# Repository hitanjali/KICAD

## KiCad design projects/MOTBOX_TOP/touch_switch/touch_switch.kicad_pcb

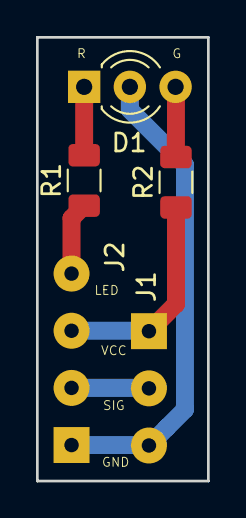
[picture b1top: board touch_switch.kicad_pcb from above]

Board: 2 copper layers, 9.5 x 24.6 mm, 5 parts (0 on the bottom side), 6 nets.

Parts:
D1: LED_Dual_ACA; LED_D3.0mm-3
J1: Conn_01x03; SolderWirePad_1x03_P3.175mm_Drill0.8mm
J2: Conn_01x04; SolderWirePad_1x04_P3.175mm_Drill0.8mm
R1, R2: 150R; R_1206_3216Metric

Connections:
unnamed: D1.1, R1.2
unnamed: D1.2, J1.3, J2.1
unnamed: D1.3, R2.2
unnamed: J1.1, J2.3, R2.1
unnamed: J1.2, J2.2
unnamed: J2.4, R1.1

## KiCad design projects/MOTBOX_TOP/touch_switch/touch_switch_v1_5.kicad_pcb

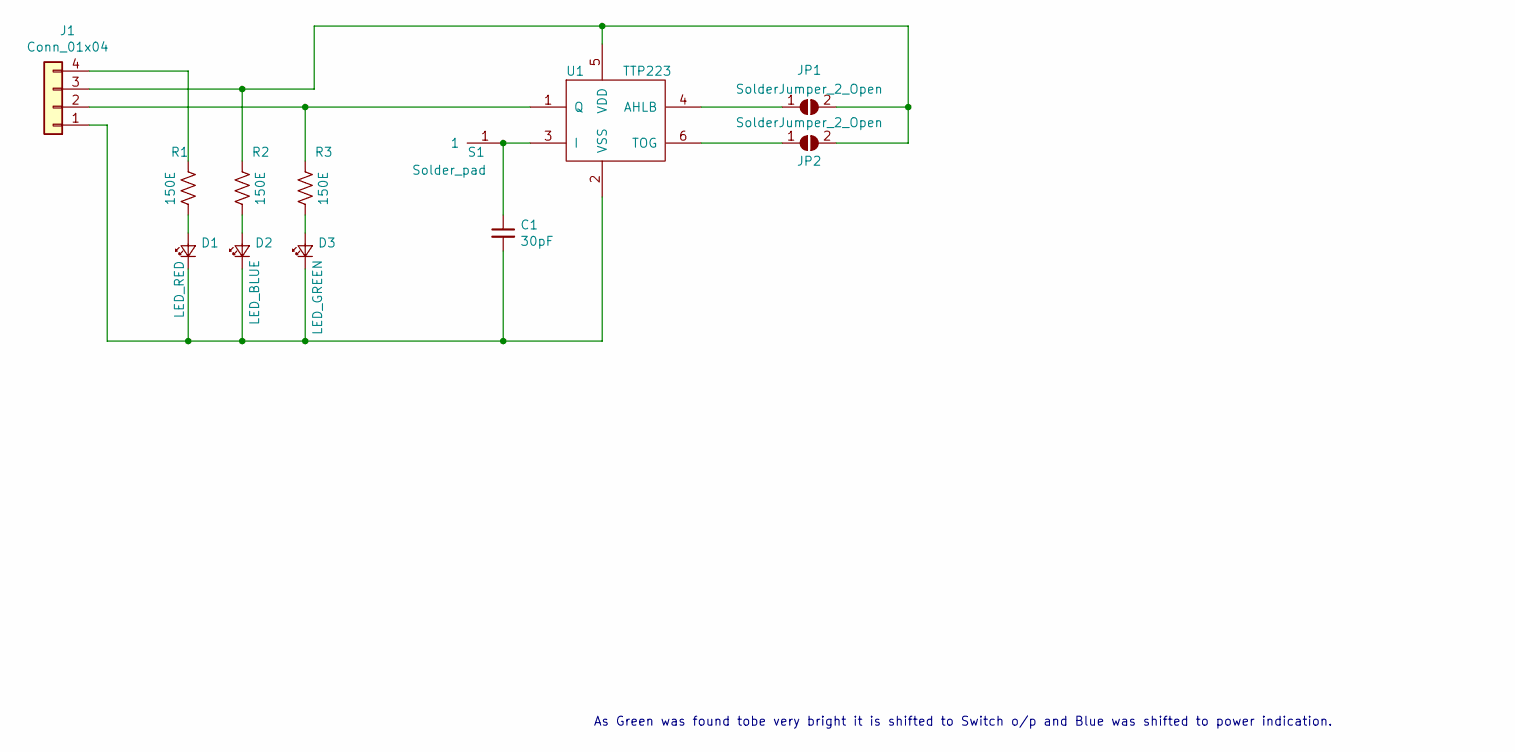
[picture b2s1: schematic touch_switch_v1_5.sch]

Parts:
C1: 30pF; C_0603_1608Metric
D1: LED_RED; LED_0603_1608Metric
D2: LED_BLUE; LED_0603_1608Metric
D3: LED_GREEN; LED_0603_1608Metric
J1: Conn_01x04; SolderWirePad_1x04_P3.175mm_Drill0.8mm
JP1, JP2: SolderJumper_2_Open; SolderJumper-2_P1.3mm_Open_RoundedPad1.0x1.5mm
R1, R2, R3: 150E; R_0603_1608Metric
S1: Solder_pad; Touch_pad_10x10mm
U1: TTP223; SOT-23-6

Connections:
unnamed: C1.1, S1.1, U1.3 (I)
unnamed: C1.2, D1.1 (K), D2.1 (K), D3.1 (K), J1.1, U1.2 (VSS)
unnamed: D1.2 (A), R1.2
unnamed: D2.2 (A), R2.2
unnamed: D3.2 (A), R3.2
unnamed: J1.2, R3.1, U1.1 (Q)
unnamed: J1.3, JP1.2 (B), JP2.2 (B), R2.1, U1.5 (VDD)
unnamed: J1.4, R1.1
unnamed: JP1.1 (A), U1.4 (AHLB)
unnamed: JP2.1 (A), U1.6 (TOG)

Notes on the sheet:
As Green was found tobe very bright it is shifted to Switch o/p and Blue was shifted to power indication.

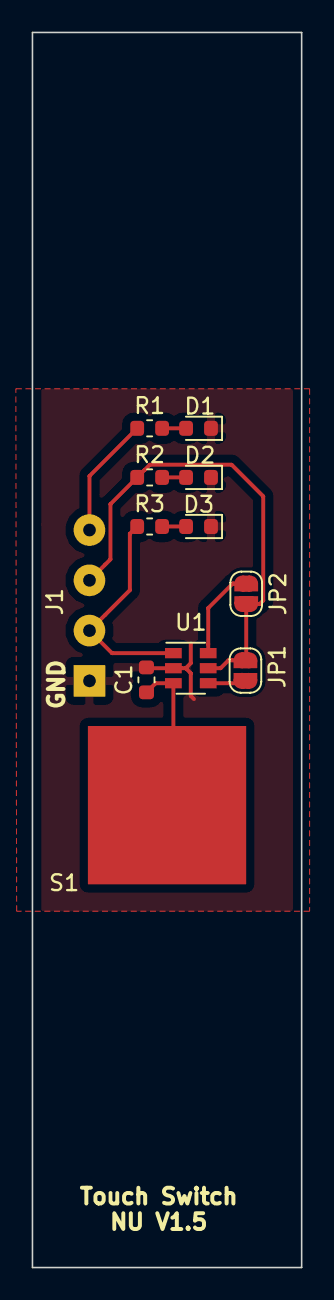
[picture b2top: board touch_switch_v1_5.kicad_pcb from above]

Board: 2 copper layers, 17.0 x 78.0 mm, 12 parts (0 on the bottom side), 10 nets.

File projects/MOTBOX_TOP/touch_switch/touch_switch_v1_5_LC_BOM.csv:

S.No,Manufacturing Part No,Designator,Quantity,Description(VALUE),Package(CASE),Top/Bottom,Points (No. of Pins),Comments,,
1,  , "C1, " , "1" , "30pF" , "Capacitor_SMD:C_0603_1608Metric" , TOP , 2, "Unpolarized capacitor, small symbol", , 
2,  , "D1, " , "1" , "LED_RED" , "LED_SMD:LED_0603_1608Metric" , TOP , 2, "Light emitting diode, small symbol", , 
3,  , "D2, " , "1" , "LED_GREEN" , "LED_SMD:LED_0603_1608Metric" , TOP , 2, "Light emitting diode, small symbol", , 
4,  , "D3, " , "1" , "LED_BLUE" , "LED_SMD:LED_0603_1608Metric" , TOP , 2, "Light emitting diode, small symbol", , 
5,  , "J1, " , "1" , "Conn_01x04" , "Connector_Wire:SolderWirePad_1x04_P3.175mm_Drill0.8mm" , TOP , 4, "Generic connector, single row, 01x04, script generated (kicad-library-utils/schlib/autogen/connector/)", , 
6,  , "JP1, JP2, " , "2" , "SolderJumper_2_Open" , "Jumper:SolderJumper-2_P1.3mm_Open_RoundedPad1.0x1.5mm" , TOP , 2, "Solder Jumper, 2-pole, open", , 
7,  , "R1, R2, R3, " , "3" , "150E" , "Resistor_SMD:R_0603_1608Metric" , TOP , 2, "Resistor, US symbol", , 
8,  , "S1, " , "1" , "Solder_pad" , "mylib:Touch_pad_10x10mm" , TOP , 1, "", , 
9,  , "U1, " , "1" , "TTP223" , "Package_TO_SOT_SMD:SOT-23-6" , TOP , 6, "", ,

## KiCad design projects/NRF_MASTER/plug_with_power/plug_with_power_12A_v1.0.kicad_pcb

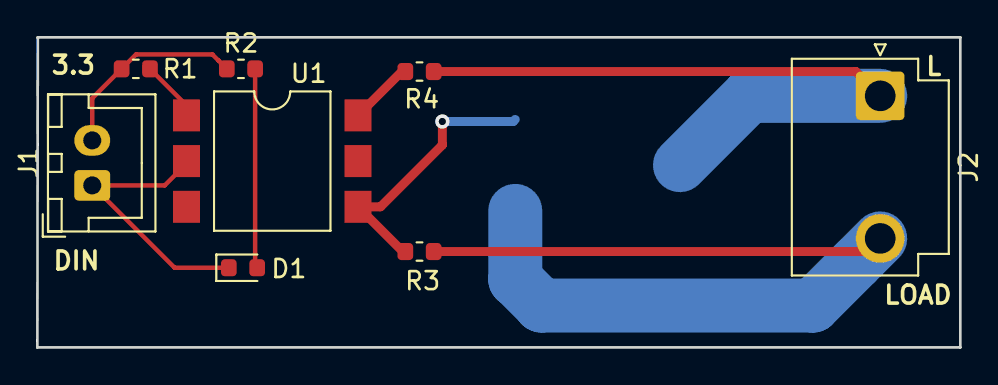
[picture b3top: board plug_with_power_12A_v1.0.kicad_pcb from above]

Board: 2 copper layers, 51.3 x 17.2 mm, 9 parts (1 on the bottom side), 8 nets.

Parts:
D1: YELLOW; LED_0603_1608Metric
D2: T12XX-600G; TO-263-2
J1: Conn_01x02; JST_XH_B2B-XH-A_1x02_P2.50mm_Vertical
J2: Conn_01x02; JST_VH_B2P3-VH_1x02_P7.92mm_Vertical
R1, R2: 220; R_0603_1608Metric
R3: 330; R_0603_1608Metric
R4: 360; R_0603_1608Metric
U1: MOC3083S; SMDIP-6_W9.53mm_Clearance8mm

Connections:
/ACHC1: D2.1, J2.2, R3.1
/ACHC2: D2.2, J2.1, R4.1
unnamed: D1.1, J1.1, U1.2
unnamed: D1.2, R2.2
unnamed: D2.3, R3.2, U1.4
unnamed: J1.2, R1.2, R2.1
unnamed: R1.1, U1.1
unnamed: R4.2, U1.6

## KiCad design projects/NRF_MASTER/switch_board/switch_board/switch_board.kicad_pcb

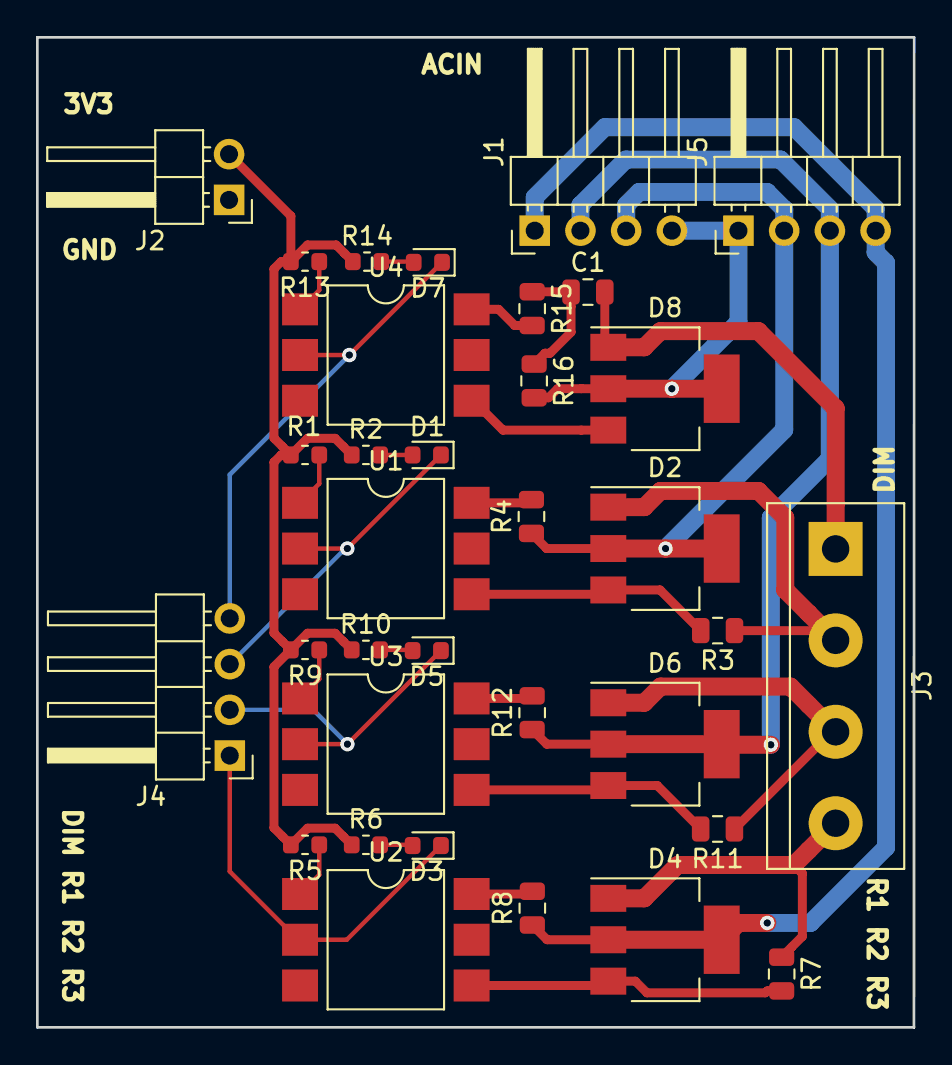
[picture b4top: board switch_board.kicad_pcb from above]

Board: 2 copper layers, 48.7 x 55.0 mm, 34 parts (0 on the bottom side), 30 nets.

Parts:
C1: C_Small; C_0805_2012Metric
D1, D3, D5, D7: YELLOW; LED_0603_1608Metric
D2, D4, D6, D8: Z0103MN; SOT-223
J1, J4, J5: Conn_01x04; PinHeader_1x04_P2.54mm_Horizontal
J2: Conn_01x02; PinHeader_1x02_P2.54mm_Horizontal
J3: Conn_01x04; TerminalBlock_bornier-4_P5.08mm
R1, R2, R5, R6, R9, R10, R13, R14: 220; R_0603_1608Metric
R3, R7, R11: 330; R_0805_2012Metric
R4, R8, R12, R15: 360; R_0805_2012Metric
R16: 470; R_0805_2012Metric
U1, U2, U3: MOC3083S; SMDIP-6_W9.53mm
U4: MOC3023MS; SMDIP-6_W9.53mm

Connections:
/ACIN1: D8.2, D8.4, J1.4, J5.1, R16.2
/ACIN2: D2.2, D2.4, J1.3, J5.2, R4.1
/ACIN3: D6.2, D6.4, J1.2, J5.3, R12.1
/ACIN4: D4.2, D4.4, J1.1, J5.4, R8.1
/ACO1: C1.2, D8.1, J3.1
/ACO2: D2.1, J3.2, R3.1
/ACO3: D6.1, J3.3, R11.1
/ACO4: D4.1, J3.4, R7.1
/Relay_1/3.3V: J2.2, R1.2, R2.1, R5.2, R6.1, R9.2, R10.1, R13.2, R14.1
/Relay_1/AL1: R4.2, U1.6
/Relay_1/AL2: D2.3, R3.2, U1.4
/Relay_1/DIN: D1.1, J4.3, U1.2
/Relay_2/AL1: R12.2, U3.6
/Relay_2/AL2: D6.3, R11.2, U3.4
/Relay_2/DIN: D5.1, J4.2, U3.2
/Relay_3/AL1: R8.2, U2.6
/Relay_3/AL2: D4.3, R7.2, U2.4
/Relay_3/DIN: D3.1, J4.1, U2.2
/dimmer_1/AL1: C1.1, R15.1, R16.1
/dimmer_1/AL2: R15.2, U4.6
/dimmer_1/AL3: D8.3, U4.4
/dimmer_1/DIN: D7.1, J4.4, U4.2
unnamed: D1.2, R2.2
unnamed: D3.2, R6.2
unnamed: D5.2, R10.2
unnamed: D7.2, R14.2
unnamed: R1.1, U1.1
unnamed: R5.1, U2.1
unnamed: R9.1, U3.1
unnamed: R13.1, U4.1

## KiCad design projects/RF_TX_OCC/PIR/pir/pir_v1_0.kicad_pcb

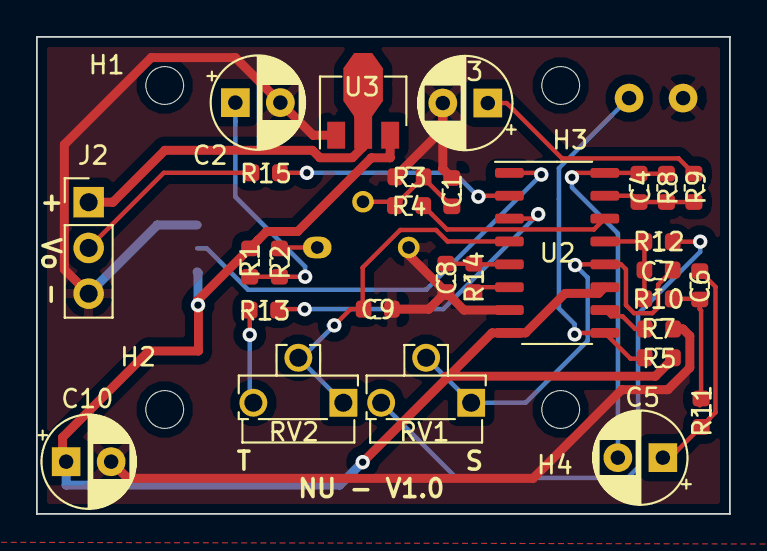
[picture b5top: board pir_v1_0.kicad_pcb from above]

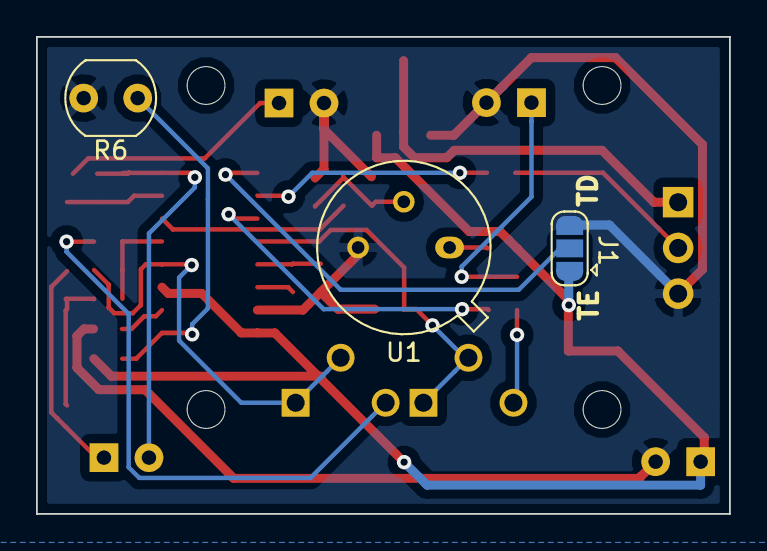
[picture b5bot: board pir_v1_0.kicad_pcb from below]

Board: 2 copper layers, 38.5 x 26.5 mm, 36 parts (3 on the bottom side), 25 nets.

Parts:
C1, C4, C7, C9: 0.01uF; C_0603_1608Metric
C2, C3: 47uF; CP_Radial_D5.0mm_P2.50mm
C5, C10: 22uF; CP_Radial_D5.0mm_P2.50mm
C6, C8: 0.1uF; C_0603_1608Metric
H1: LT; MountingHole_2.1mm
H2: LB; MountingHole_2.1mm
H3: RT; MountingHole_2.1mm
H4: RB; MountingHole_2.1mm
J1: Conn_01x03_Male; SolderJumper-3_P1.3mm_Open_RoundedPad1.0x1.5mm
J2: Conn_01x03; PinHeader_1x03_P2.54mm_Vertical
R1, R13: 10K; R_0603_1608Metric
R2, R4, R8: 18K; R_0603_1608Metric
R3: 47K; R_0603_1608Metric
R5: 100K; R_0603_1608Metric
R6: LDR_5mm; R_LDR_5.0x4.1mm_P3mm_Vertical
R7, R9, R14: 1M; R_0603_1608Metric
R10: 6.8K; R_0603_1608Metric
R11: 2K; R_0603_1608Metric
R12: 470K; R_0603_1608Metric
R15: 1K; R_0603_1608Metric
RV1, RV2: 1M; Potentiometer_Runtron_RM-063_Horizontal
U1: D203S; TO-5-3_Window
U2: BISS0001; STC_SOP-16_3.9x9.9mm_P1.27mm
U3: HT7133; SOT-89-3

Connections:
+3V3: C10.1, J1.1, R1.1, R5.1, U2.8, U2.11, U3.3
GND: C1.2, C2.2, C3.2, C8.1, C9.1, C10.2, J1.3, J2.3, R3.2, R6.2, R7.2, U1.3, U2.7, U3.1
unnamed: C1.1, R3.1, R4.2, U1.2
unnamed: C2.1, R1.2, R2.1
unnamed: C3.1, R8.2
unnamed: C4.1, C5.2, R9.1, U2.16
unnamed: C4.2, R8.1, R9.2, U2.15
unnamed: C5.1, C6.1, R11.1
unnamed: C6.2, R10.1, R11.2
unnamed: C7.1, R10.2, R12.1, U2.13
unnamed: C7.2, RV1.1, RV1.2, U2.12
unnamed: C8.2, R14.1, U2.5
unnamed: C9.2, RV2.1, RV2.2, U2.4
unnamed: J1.2, U2.1
unnamed: J2.1, U3.2
unnamed: J2.2, R15.1
unnamed: R2.2, U1.1
unnamed: R4.1, U2.14
unnamed: R5.2, R6.1, U2.9
unnamed: R7.1, U2.10
unnamed: R12.2, RV1.3
unnamed: R13.1, RV2.3
unnamed: R13.2, U2.3
unnamed: R14.2, U2.6
unnamed: R15.2, U2.2

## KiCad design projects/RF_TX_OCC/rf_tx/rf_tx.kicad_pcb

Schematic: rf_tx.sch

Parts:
C1: 330uF; CP_Radial_D8.0mm_P3.80mm
C2: 1uF; C_0805_2012Metric_Pad1.15x1.40mm_HandSolder
C3: 30pF; C_0603_1608Metric_Pad1.05x0.95mm_HandSolder
J1: Conn_01x03; PinSocket_1x03_P2.54mm_Vertical
J2, J3: Conn_02x03_Odd_Even; PinHeader_2x03_P2.54mm_Vertical
J4: Conn_01x02; PinHeader_1x02_P2.54mm_Vertical
J5: Conn_01x04; PinSocket_1x04_P2.54mm_Vertical
J6: Conn_01x01_Female; SolderWirePad_1x01_Drill1.2mm
PCB1: 433MHz TX
R1: 1K; R_0603_1608Metric_Pad1.05x0.95mm_HandSolder
R2: 100K; R_0603_1608Metric_Pad1.05x0.95mm_HandSolder
R3: 1M; R_0603_1608Metric_Pad1.05x0.95mm_HandSolder
R4: 470K; R_0603_1608Metric_Pad1.05x0.95mm_HandSolder
SW1: SW_DIP_x08; DIP-16_W7.62mm_LongPads
SW2: SW_DIP_x02; DIP-4_W7.62mm_LongPads
U1: 74LVC1G125; SOT-353_SC-70-5_Handsoldering
U2: 74LVC1G14; TSOP-5_1.65x3.05mm_P0.95mm
U3: 74LVC1G86; SOT-353_SC-70-5_Handsoldering
U4: HT12E; DIP-18_W7.62mm_Socket_LongPads
U5: 74LVC1G04; SOT-23-5_HandSoldering
U6: 74LVC1G04; TSOT-23-5_HandSoldering
U7: BD48ExxG; TSOP-5_1.65x3.05mm_P0.95mm

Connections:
/ANT: J5.1, J6.1
/BAT_LOW: C3.1, R4.2, U4.12 (AD10), U7.1
/DATA: J5.3, U4.17 (DOUT)
/OUT: J2.6, J3.5, R1.1, U3.1, U4.13 (AD11)
/SENSOR: J1.2, J2.4, J3.3
GND: C1.2, C2.2, C3.2, J1.1, J4.1, J5.4, SW1.1, SW1.2, SW1.3, SW1.4, SW1.5, SW1.6, SW1.7, SW1.8, SW2.3, SW2.4, U1.1, U1.3, U2.3 (GND), U3.3 (GND), U4.9 (VSS), U5.3, U6.3, U7.3
unnamed: C1.1, R1.2, U2.2
unnamed: J2.1, U1.5
unnamed: J2.3, U1.2
unnamed: J2.5, U1.4
unnamed: J3.2, U5.5, U6.5
unnamed: J3.4, U5.2
unnamed: J3.6, U6.4
unnamed: R2.1, R3.1
unnamed: R2.2, U4.16 (OSC1)
unnamed: R3.2, U4.15 (OSC2)
unnamed: SW1.9, U4.8 (A7)
unnamed: SW1.10, U4.7 (A6)
unnamed: SW1.11, U4.6 (A5)
unnamed: SW1.12, U4.5 (A4)
unnamed: SW1.13, U4.4 (A3)
unnamed: SW1.14, U4.3 (A2)
unnamed: SW1.15, U4.2 (A1)
unnamed: SW1.16, U4.1 (A0)
unnamed: SW2.1, U4.11 (AD9)
unnamed: SW2.2, U4.10 (AD8)
unnamed: U2.4, U3.2
unnamed: U3.4, U4.14 (TE)
unnamed: U5.4, U6.2
VCC: C2.1, J1.3, J2.2, J3.1, J4.2, J5.2, R4.1, U2.5 (VCC), U3.5 (VCC), U4.18 (VDD), U7.2

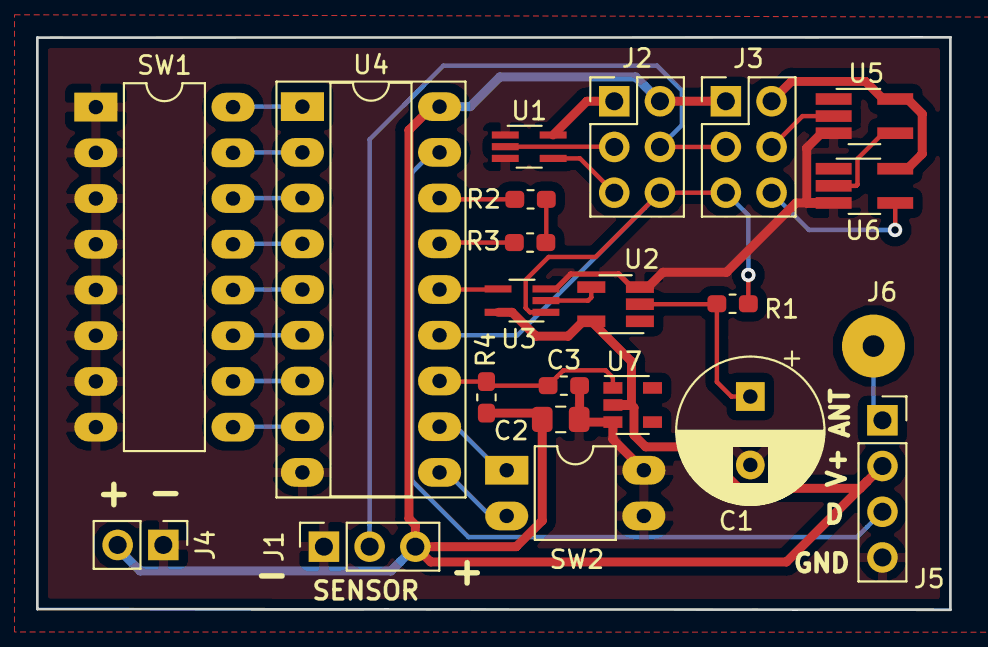
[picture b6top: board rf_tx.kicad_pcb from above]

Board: 2 copper layers, 50.7 x 31.8 mm, 22 parts (0 on the bottom side), 30 nets.
